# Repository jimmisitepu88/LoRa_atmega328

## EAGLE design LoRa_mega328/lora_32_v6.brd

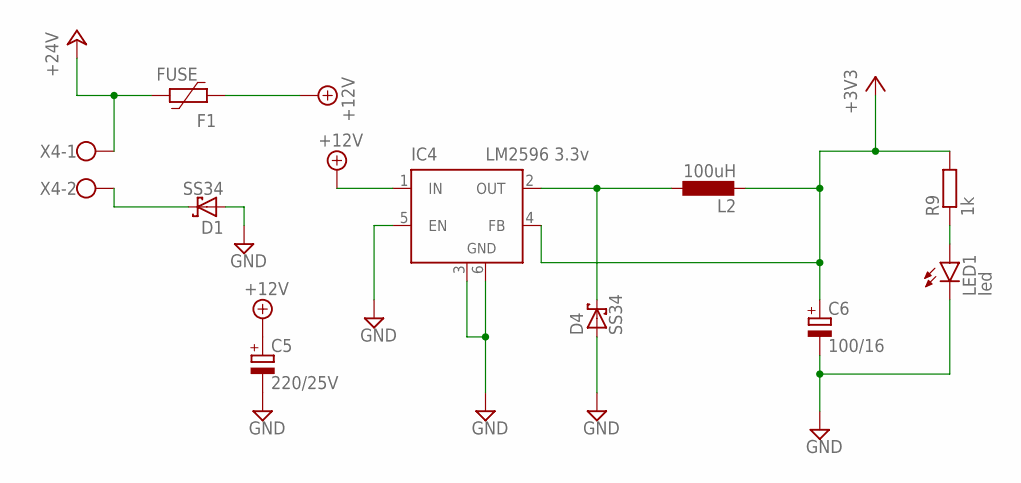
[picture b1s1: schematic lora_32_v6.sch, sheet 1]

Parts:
C5: 220/25V; PANASONIC_G
C6: 100/16; 140CLH-0810
D1, D4: SS34; SMB
F1: FUSE; 1812L
IC4: LM2596 3.3v; TO263-5
L2: 100uH; 6000-XXXX-RC
LED1: led; SML0805
R9: 1k; M0805
X4: W237-102

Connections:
+3V3: C6.+, IC4.4 (FB), L2.2, R9.2; also elsewhere on the board
+12V: C5.+, F1.2, IC4.1 (IN)
+24V: F1.1, X4.1; also elsewhere on the board
GND: C5.-, C6.-, D1.A, D4.A, IC4.3 (GND), IC4.5 (EN), IC4.6 (GND), LED1.C; also elsewhere on the board
unnamed: D4.C, IC4.2 (OUT), L2.1
unnamed: LED1.A, R9.1
unnamed: D1.C, X4.2

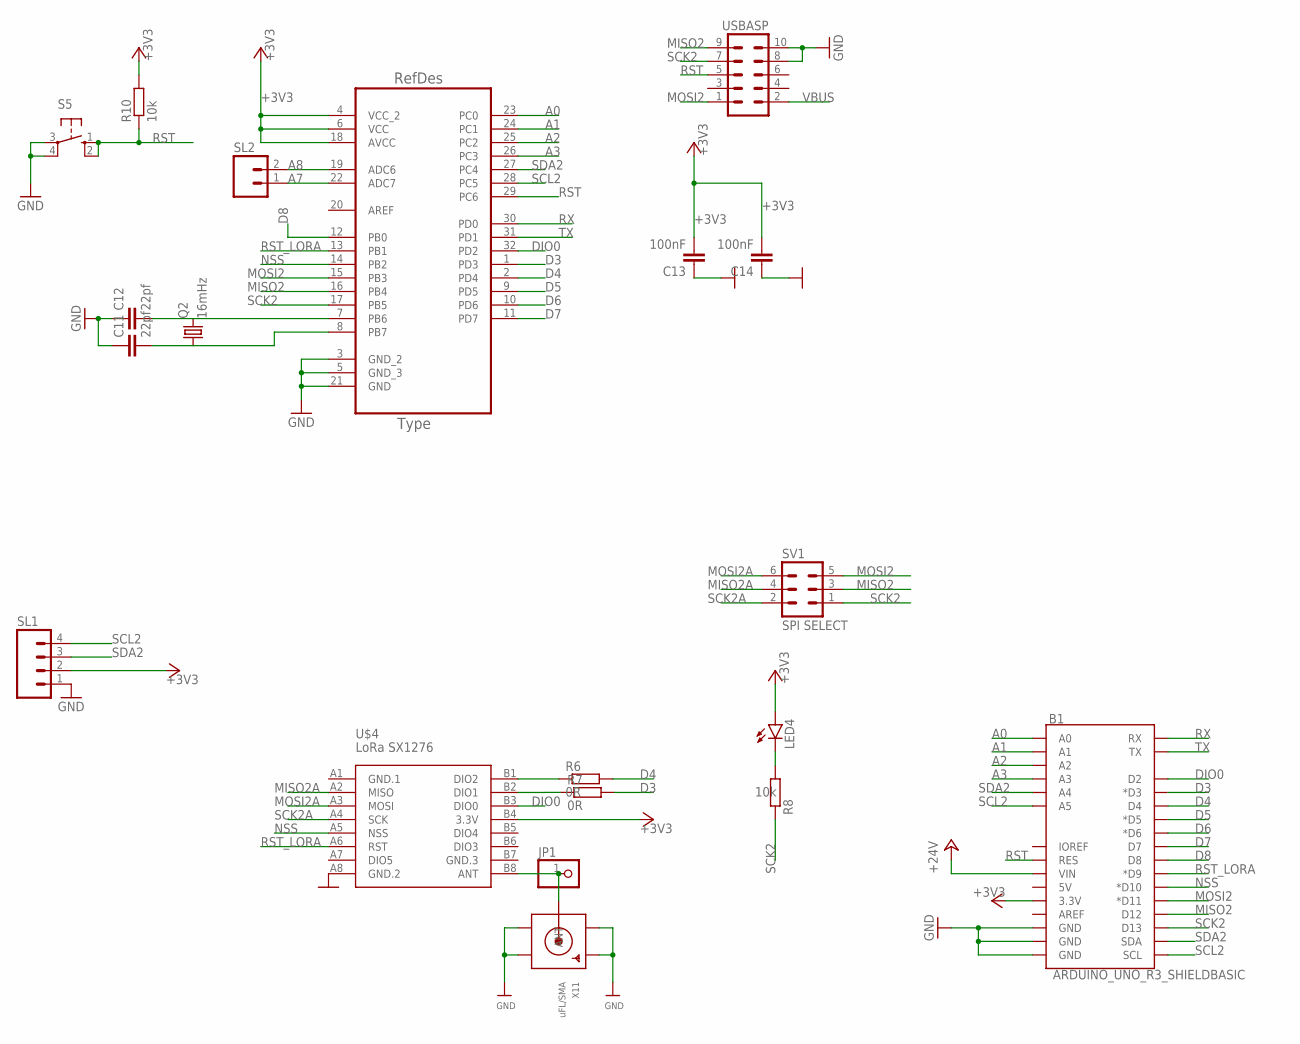
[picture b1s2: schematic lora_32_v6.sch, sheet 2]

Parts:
B1: ARDUINO_UNO_R3_SHIELDBASIC; UNO_R3_SHIELD
C11, C12: 22pf; C0805K
C13, C14: 100nF; C0805K
JP1: HEADER-1X1ROUND; 1X01_ROUND
LED4: LEDSML0805; SML0805
Q2: 16mHz; HC49UP
R6, R7: 0R; M0805
R8, R10: 10k; M0805
S5: 10-XX; B3F-10XX
SL1: M04; 04P
SL2: M02; 02P
SV1: SPI SELECT; MA03-2
U1: ATMEGA328P-AU; QFP80P900X900X120-32N
U$4: LoRa SX1276; WIRELESS-LORA-RFM95W#SMD
USBASP: MA05-2
X11: uFL/SMA; SMA_EDGELAUNCH_UFL

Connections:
+3V3: B1.3.3V, C13.2, C14.2, LED4.A, R10.2, SL1.2, U1.4 (VCC_2), U1.6 (VCC), U1.18 (AVCC), U$4.B4 (3.3V); also elsewhere on the board
+24V: B1.VIN; also elsewhere on the board
A0: B1.A0, U1.23 (PC0)
A1: B1.A1, U1.24 (PC1)
A2: B1.A2, U1.25 (PC2)
A3: B1.A3, U1.26 (PC3)
A7: SL2.1, U1.22 (ADC7)
A8: SL2.2, U1.19 (ADC6)
D3: B1.D3 (*D3), R7.2, U1.1 (PD3)
D4: B1.D4, R6.2, U1.2 (PD4)
D5: B1.D5 (*D5), U1.9 (PD5)
D6: B1.D6 (*D6), U1.10 (PD6)
D7: B1.D7, U1.11 (PD7)
D8: B1.D8, U1.12 (PB0)
DIO0: B1.D2, U1.32 (PD2), U$4.B3 (DIO0)
GND: B1.GND@0 (GND), B1.GND@1 (GND), B1.GND@2 (GND), C11.1, C12.1, C13.1, C14.1, S5.3, S5.4 (P1), SL1.1, U1.3 (GND_2), U1.5 (GND_3), U1.21 (GND), U$4.A8 (GND.2), USBASP.8, USBASP.10, X11.GND@1 (GND1), X11.GND@2 (GND2), X11.GND@3 (GND3), X11.GND@4 (GND4); also elsewhere on the board
GND.1: U$4.A1 (GND.1)
GND.3: U$4.B7 (GND.3)
MISO2: B1.D12, SV1.3, U1.16 (PB4), USBASP.9
MISO2A: SV1.4, U$4.A2 (MISO)
MOSI2: B1.D11 (*D11), SV1.5, U1.15 (PB3), USBASP.1
MOSI2A: SV1.6, U$4.A3 (MOSI)
unnamed: C12.2, Q2.2, U1.7 (PB6)
unnamed: C11.2, Q2.1, U1.8 (PB7)
unnamed: R7.1, U$4.B2 (DIO1)
unnamed: R6.1, U$4.B1 (DIO2)
unnamed: LED4.C, R8.1
unnamed: JP1.1, U$4.B8 (ANT), X11.P (ANT)
NSS: B1.D10 (*D10), U1.14 (PB2), U$4.A5 (NSS)
RST: B1.RES, R10.1, S5.1 (S), S5.2 (S1), U1.29 (PC6), USBASP.5; also elsewhere on the board
RST_LORA: B1.D9 (*D9), U1.13 (PB1), U$4.A6 (RST)
RX: B1.RX, U1.30 (PD0); also elsewhere on the board
SCK2: B1.D13, R8.2, SV1.1, U1.17 (PB5), USBASP.7
SCK2A: SV1.2, U$4.A4 (SCK)
SCL2: B1.A5, B1.SCL, SL1.4, U1.28 (PC5)
SDA2: B1.A4, B1.SDA, SL1.3, U1.27 (PC4)
TX: B1.TX, U1.31 (PD1); also elsewhere on the board
VBUS: USBASP.2; also elsewhere on the board

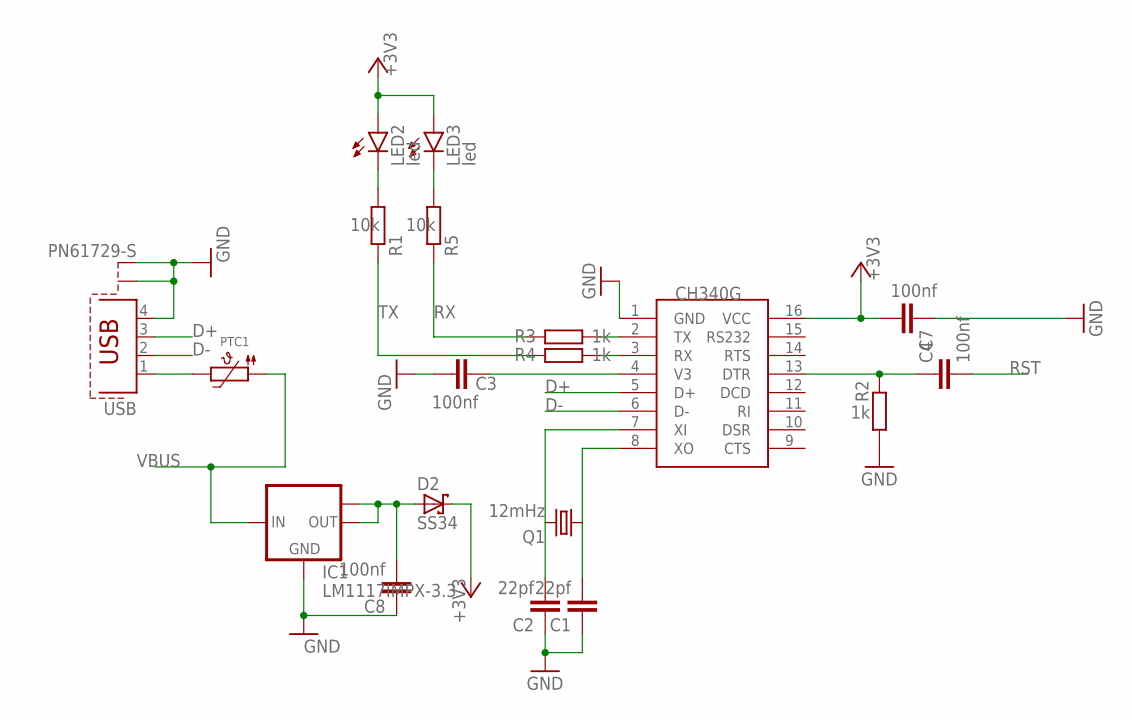
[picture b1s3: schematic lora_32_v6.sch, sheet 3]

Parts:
C1, C2: 22pf; C0805K
C3, C4, C7, C8: 100nf; C0805K
D2: SS34; SMB
IC1: LM1117IMPX-3.3; SOT223
LED2, LED3: led; SML0805
PTC1: PTC1206; 1206
Q1: 12mHz; HC49UP
R1, R5: 10k; M0805
R2, R3, R4: 1k; M0805
U$5: CH340G; SOIC16
USB: PN61729-S

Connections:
+3V3: C7.2, D2.C, LED2.A, LED3.A, U$5.16 (VCC); also elsewhere on the board
D+: U$5.5 (D+), USB.3
D-: U$5.6 (D-), USB.2
GND: C1.1, C2.1, C3.1, C7.1, C8.1, IC1.1 (GND), R2.1, U$5.1 (GND), USB.4, USB.S1, USB.S2; also elsewhere on the board
unnamed: C2.2, Q1.2, U$5.7 (XI)
unnamed: C1.2, Q1.1, U$5.8 (XO)
unnamed: C3.2, U$5.4 (V3)
unnamed: C4.1, R2.2, U$5.13 (DTR)
unnamed: R3.1, U$5.2 (TX)
unnamed: R4.1, U$5.3 (RX)
unnamed: PTC1.2, USB.1
unnamed: C8.2, D2.A, IC1.2 (OUT), IC1.TAB (OUT1)
unnamed: LED3.C, R5.1
unnamed: LED2.C, R1.1
RST: C4.2; also elsewhere on the board
RX: R3.2, R5.2; also elsewhere on the board
TX: R1.2, R4.2; also elsewhere on the board
VBUS: IC1.3 (IN), PTC1.1; also elsewhere on the board

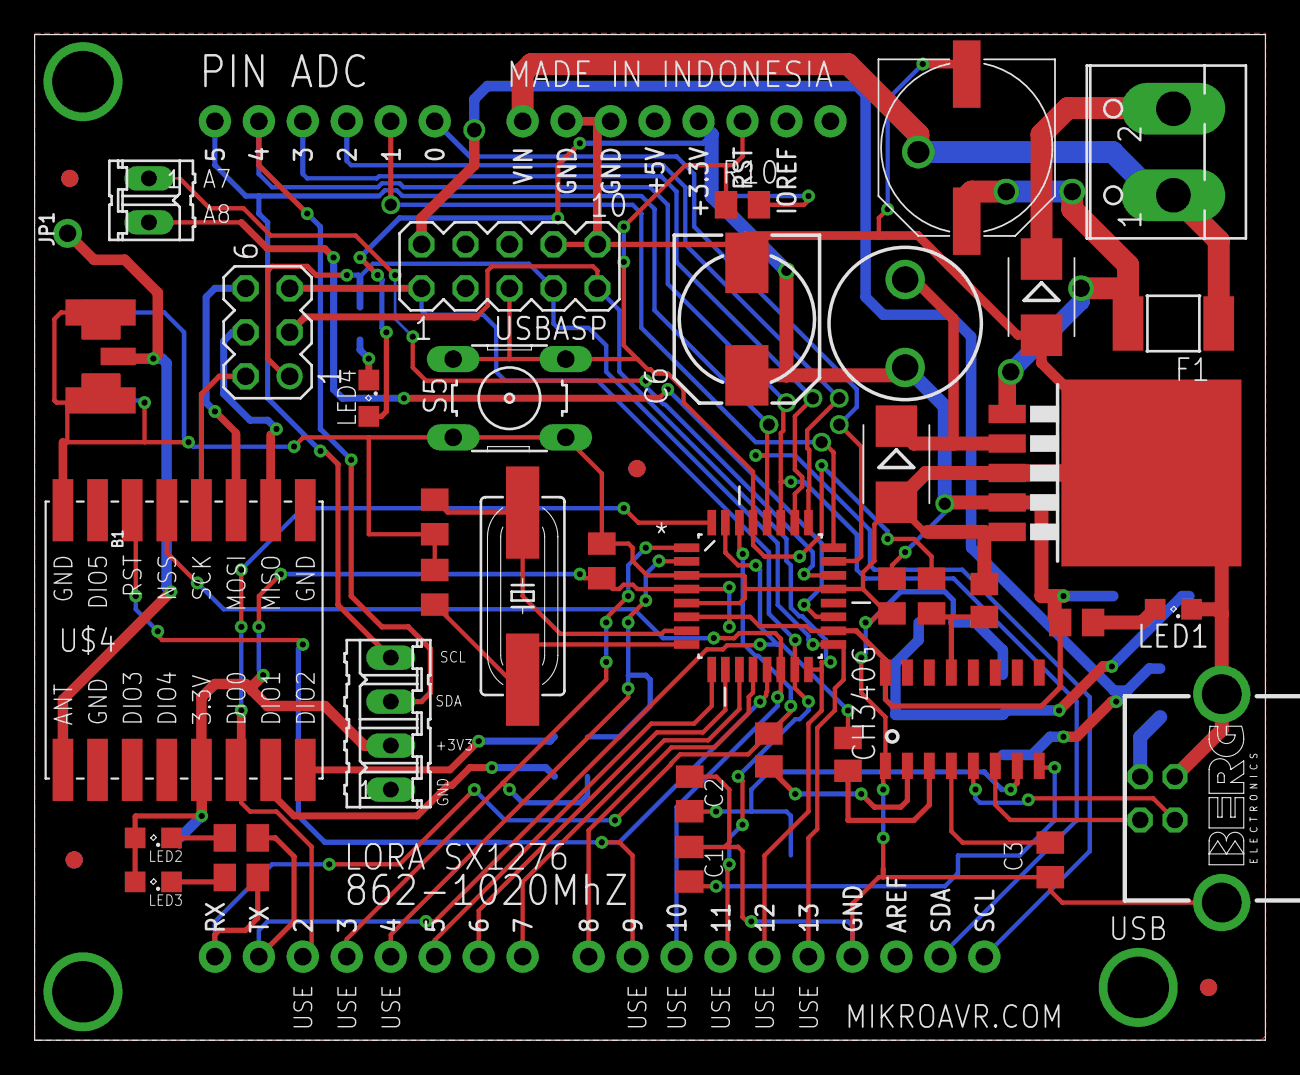
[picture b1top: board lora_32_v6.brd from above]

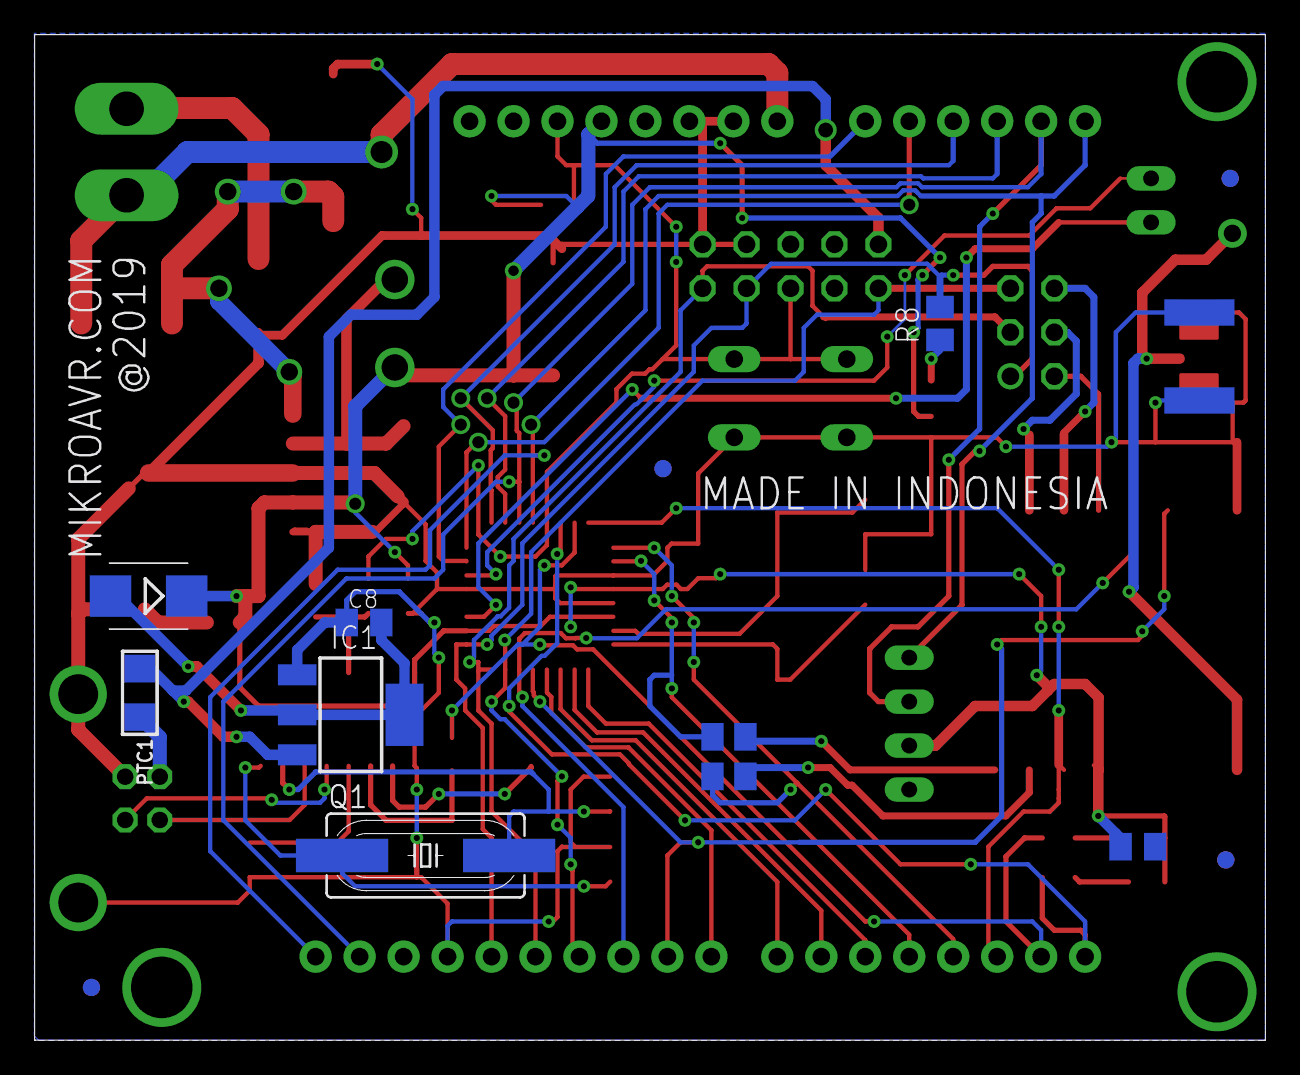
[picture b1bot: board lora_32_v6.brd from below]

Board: 2 copper layers, 71.1 x 58.1 mm, 53 parts (9 on the bottom side), 52 nets.

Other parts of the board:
U$3, U$6, U$7, U$8: CIRCLE-1MM-2R

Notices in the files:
parts and their libraries:
diy-modules: Released under the Creative Commons Attribution 4.0 International License: http://creativecommons.org/licenses/by/4.0
microbuilder: This work is placed in the public domain, and may be freely used for commercial and non-commercial work with the following conditions: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
